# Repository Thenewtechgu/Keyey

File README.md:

# Keyey
A custom made 75 percent keyboard powered by the RP2040.

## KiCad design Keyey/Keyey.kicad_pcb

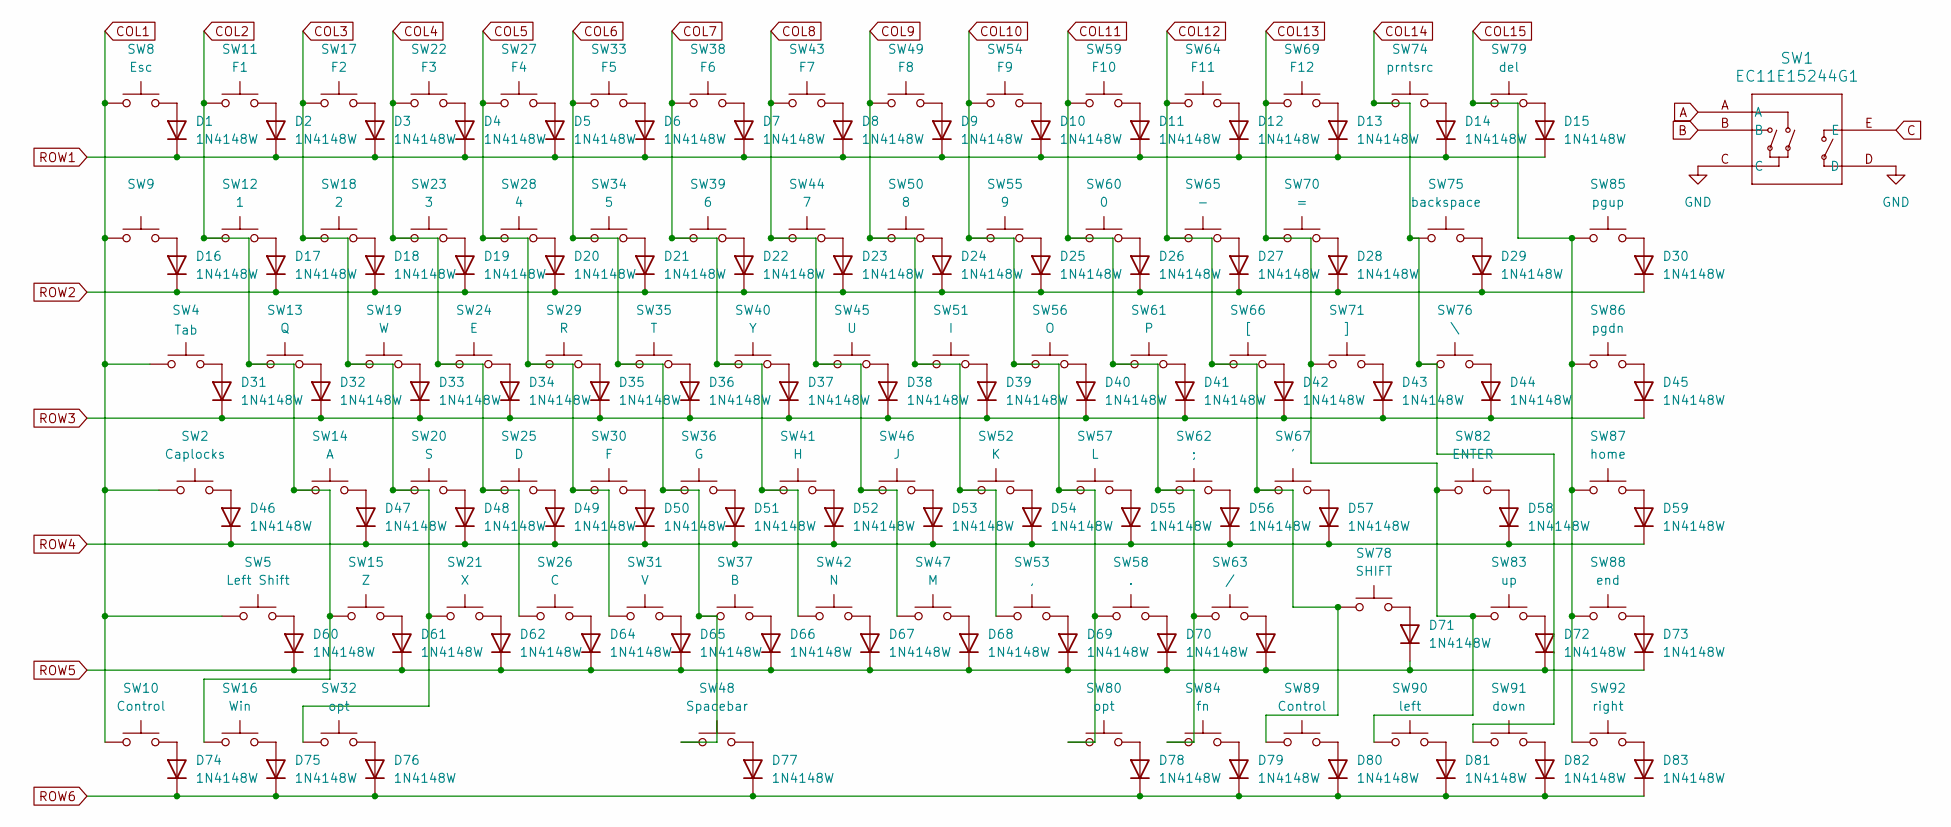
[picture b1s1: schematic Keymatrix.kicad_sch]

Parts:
D1, D2, D3, D4, D5, D6, D7, D8, D9, D10, D11, D12, D13, D14, D15, D16, D17, D18, D19, D20, D21, D22, D23, D24, D25, D26, D27, D28, D29, D30, D31, D32, D33, D34, D35, D36, D37, D38, D39, D40, D41, D42, D43, D44, D45, D46, D47, D48, D49, D50, D51, D52, D53, D54, D55, D56, D57, D58, D59, D60, D61, D62, D63, D64, D65, D66, D67, D68, D69, D70, D71, D72, D73, D74, D75, D76, D77, D78, D79, D80, D81, D82, D83: 1N4148W; D_SOD-123
SW1: EC11E15244G1; EC11E15244G1_AAL
SW2: Caplocks; SW_MX_1u
SW4: Tab; SW_MX_1u
SW5: Left Shift; SW_MX_1u
SW8: Esc; SW_MX_1u
SW9: SW_MX_1u
SW10, SW89: Control; SW_MX_1u
SW11: F1; SW_MX_1u
SW12: 1; SW_MX_1u
SW13: Q; SW_MX_1u
SW14: A; SW_MX_1u
SW15: Z; SW_MX_1u
SW16: Win; SW_MX_1u
SW17: F2; SW_MX_1u
SW18: 2; SW_MX_1u
SW19: W; SW_MX_1u
SW20: S; SW_MX_1u
SW21: X; SW_MX_1u
SW22: F3; SW_MX_1u
SW23: 3; SW_MX_1u
SW24: E; SW_MX_1u
SW25: D; SW_MX_1u
SW26: C; SW_MX_1u
SW27: F4; SW_MX_1u
SW28: 4; SW_MX_1u
SW29: R; SW_MX_1u
SW30: F; SW_MX_1u
SW31: V; SW_MX_1u
SW32, SW80: opt; SW_MX_1u
SW33: F5; SW_MX_1u
SW34: 5; SW_MX_1u
SW35: T; SW_MX_1u
SW36: G; SW_MX_1u
SW37: B; SW_MX_1u
SW38: F6; SW_MX_1u
SW39: 6; SW_MX_1u
SW40: Y; SW_MX_1u
SW41: H; SW_MX_1u
SW42: N; SW_MX_1u
SW43: F7; SW_MX_1u
SW44: 7; SW_MX_1u
SW45: U; SW_MX_1u
SW46: J; SW_MX_1u
SW47: M; SW_MX_1u
SW48: Spacebar; SW_MX_1u
SW49: F8; SW_MX_1u
SW50: 8; SW_MX_1u
SW51: I; SW_MX_1u
SW52: K; SW_MX_1u
SW53: ,; SW_MX_1u
SW54: F9; SW_MX_1u
SW55: 9; SW_MX_1u
SW56: O; SW_MX_1u
SW57: L; SW_MX_1u
SW58: .; SW_MX_1u
SW59: F10; SW_MX_1u
SW60: 0; SW_MX_1u
SW61: P; SW_MX_1u
SW62: ;; SW_MX_1u
SW63: /; SW_MX_1u
SW64: F11; SW_MX_1u
SW65: -; SW_MX_1u
SW66: [; SW_MX_1u
SW67: '; SW_MX_1u
SW69: F12; SW_MX_1u
SW70: =; SW_MX_1u
SW71: ]; SW_MX_1u
SW74: prntsrc; SW_MX_1u
SW75: backspace; SW_MX_1u
SW76: \; SW_MX_1u
SW78: SHIFT; SW_MX_1u
SW79: del; SW_MX_1u
SW82: ENTER; SW_MX_1u
SW83: up; SW_MX_1u
SW84: fn; SW_MX_1u
SW85: pgup; SW_MX_1u
SW86: pgdn; SW_MX_1u
SW87: home; SW_MX_1u
SW88: end; SW_MX_1u
SW90: left; SW_MX_1u
SW91: down; SW_MX_1u
SW92: right; SW_MX_1u

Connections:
A: SW1.A; also elsewhere on the board
B: SW1.B; also elsewhere on the board
COL1: SW2.1, SW4.1, SW5.1, SW8.1, SW9.1, SW10.1; also elsewhere on the board
COL2: SW11.1, SW12.1, SW13.1, SW14.1, SW15.1, SW16.1; also elsewhere on the board
COL3: SW17.1, SW18.1, SW19.1, SW20.1, SW21.1, SW32.1; also elsewhere on the board
COL4: SW22.1, SW23.1, SW24.1, SW25.1, SW26.1; also elsewhere on the board
COL5: SW27.1, SW28.1, SW29.1, SW30.1, SW31.1; also elsewhere on the board
COL6: SW33.1, SW34.1, SW35.1, SW36.1, SW37.1, SW48.1; also elsewhere on the board
COL7: SW38.1, SW39.1, SW40.1, SW41.1, SW42.1; also elsewhere on the board
COL8: SW43.1, SW44.1, SW45.1, SW46.1, SW47.1; also elsewhere on the board
COL9: SW49.1, SW50.1, SW51.1, SW52.1, SW53.1; also elsewhere on the board
COL10: SW54.1, SW55.1, SW56.1, SW57.1, SW58.1, SW80.1; also elsewhere on the board
COL11: SW59.1, SW60.1, SW61.1, SW62.1, SW63.1, SW84.1; also elsewhere on the board
COL12: SW64.1, SW65.1, SW66.1, SW67.1, SW78.1, SW89.1; also elsewhere on the board
COL13: SW69.1, SW70.1, SW71.1, SW82.1, SW83.1, SW90.1; also elsewhere on the board
COL14: SW74.1, SW75.1, SW76.1, SW91.1; also elsewhere on the board
COL15: SW79.1, SW85.1, SW86.1, SW87.1, SW88.1, SW92.1; also elsewhere on the board
GND: SW1.C, SW1.D; also elsewhere on the board
unnamed: D1.2 (A), SW8.2
unnamed: D2.2 (A), SW11.2
unnamed: D3.2 (A), SW17.2
unnamed: D4.2 (A), SW22.2
unnamed: D5.2 (A), SW27.2
unnamed: D6.2 (A), SW33.2
unnamed: D7.2 (A), SW38.2
unnamed: D8.2 (A), SW43.2
unnamed: D9.2 (A), SW49.2
unnamed: D10.2 (A), SW54.2
unnamed: D11.2 (A), SW59.2
unnamed: D12.2 (A), SW64.2
unnamed: D13.2 (A), SW69.2
unnamed: D14.2 (A), SW74.2
unnamed: D15.2 (A), SW79.2
unnamed: D16.2 (A), SW9.2
unnamed: D17.2 (A), SW12.2
unnamed: D18.2 (A), SW18.2
unnamed: D19.2 (A), SW23.2
unnamed: D20.2 (A), SW28.2
unnamed: D21.2 (A), SW34.2
unnamed: D22.2 (A), SW39.2
unnamed: D23.2 (A), SW44.2
unnamed: D24.2 (A), SW50.2
unnamed: D25.2 (A), SW55.2
unnamed: D26.2 (A), SW60.2
unnamed: D27.2 (A), SW65.2
unnamed: D28.2 (A), SW70.2
unnamed: D29.2 (A), SW75.2
unnamed: D30.2 (A), SW85.2
unnamed: D31.2 (A), SW4.2
unnamed: D32.2 (A), SW13.2
unnamed: D33.2 (A), SW19.2
unnamed: D34.2 (A), SW24.2
unnamed: D35.2 (A), SW29.2
unnamed: D36.2 (A), SW35.2
unnamed: D37.2 (A), SW40.2
unnamed: D38.2 (A), SW45.2
unnamed: D39.2 (A), SW51.2
unnamed: D40.2 (A), SW56.2
unnamed: D41.2 (A), SW61.2
unnamed: D42.2 (A), SW66.2
unnamed: D43.2 (A), SW71.2
unnamed: D44.2 (A), SW76.2
unnamed: D45.2 (A), SW86.2
unnamed: D46.2 (A), SW2.2
unnamed: D47.2 (A), SW14.2
unnamed: D48.2 (A), SW20.2
unnamed: D49.2 (A), SW25.2
unnamed: D50.2 (A), SW30.2
unnamed: D51.2 (A), SW36.2
unnamed: D52.2 (A), SW41.2
unnamed: D53.2 (A), SW46.2
unnamed: D54.2 (A), SW52.2
unnamed: D55.2 (A), SW57.2
unnamed: D56.2 (A), SW62.2
unnamed: D57.2 (A), SW67.2
unnamed: D58.2 (A), SW82.2
unnamed: D59.2 (A), SW87.2
unnamed: D60.2 (A), SW5.2
unnamed: D61.2 (A), SW15.2
unnamed: D62.2 (A), SW21.2
unnamed: D63.2 (A), SW63.2
unnamed: D64.2 (A), SW26.2
unnamed: D65.2 (A), SW31.2
unnamed: D66.2 (A), SW37.2
unnamed: D67.2 (A), SW42.2
unnamed: D68.2 (A), SW47.2
unnamed: D69.2 (A), SW53.2
unnamed: D70.2 (A), SW58.2
unnamed: D71.2 (A), SW78.2
unnamed: D72.2 (A), SW83.2
unnamed: D73.2 (A), SW88.2
unnamed: D74.2 (A), SW10.2
unnamed: D75.2 (A), SW16.2
unnamed: D76.2 (A), SW32.2
unnamed: D77.2 (A), SW48.2
unnamed: D78.2 (A), SW80.2
unnamed: D79.2 (A), SW84.2
unnamed: D80.2 (A), SW89.2
unnamed: D81.2 (A), SW90.2
unnamed: D82.2 (A), SW91.2
unnamed: D83.2 (A), SW92.2
ROW1: D1.1 (K), D2.1 (K), D3.1 (K), D4.1 (K), D5.1 (K), D6.1 (K), D7.1 (K), D8.1 (K), D9.1 (K), D10.1 (K), D11.1 (K), D12.1 (K), D13.1 (K), D14.1 (K), D15.1 (K); also elsewhere on the board
ROW2: D16.1 (K), D17.1 (K), D18.1 (K), D19.1 (K), D20.1 (K), D21.1 (K), D22.1 (K), D23.1 (K), D24.1 (K), D25.1 (K), D26.1 (K), D27.1 (K), D28.1 (K), D29.1 (K), D30.1 (K); also elsewhere on the board
ROW3: D31.1 (K), D32.1 (K), D33.1 (K), D34.1 (K), D35.1 (K), D36.1 (K), D37.1 (K), D38.1 (K), D39.1 (K), D40.1 (K), D41.1 (K), D42.1 (K), D43.1 (K), D44.1 (K), D45.1 (K); also elsewhere on the board
ROW4: D46.1 (K), D47.1 (K), D48.1 (K), D49.1 (K), D50.1 (K), D51.1 (K), D52.1 (K), D53.1 (K), D54.1 (K), D55.1 (K), D56.1 (K), D57.1 (K), D58.1 (K), D59.1 (K); also elsewhere on the board
ROW5: D60.1 (K), D61.1 (K), D62.1 (K), D63.1 (K), D64.1 (K), D65.1 (K), D66.1 (K), D67.1 (K), D68.1 (K), D69.1 (K), D70.1 (K), D71.1 (K), D72.1 (K), D73.1 (K); also elsewhere on the board
ROW6: D74.1 (K), D75.1 (K), D76.1 (K), D77.1 (K), D78.1 (K), D79.1 (K), D80.1 (K), D81.1 (K), D82.1 (K), D83.1 (K); also elsewhere on the board

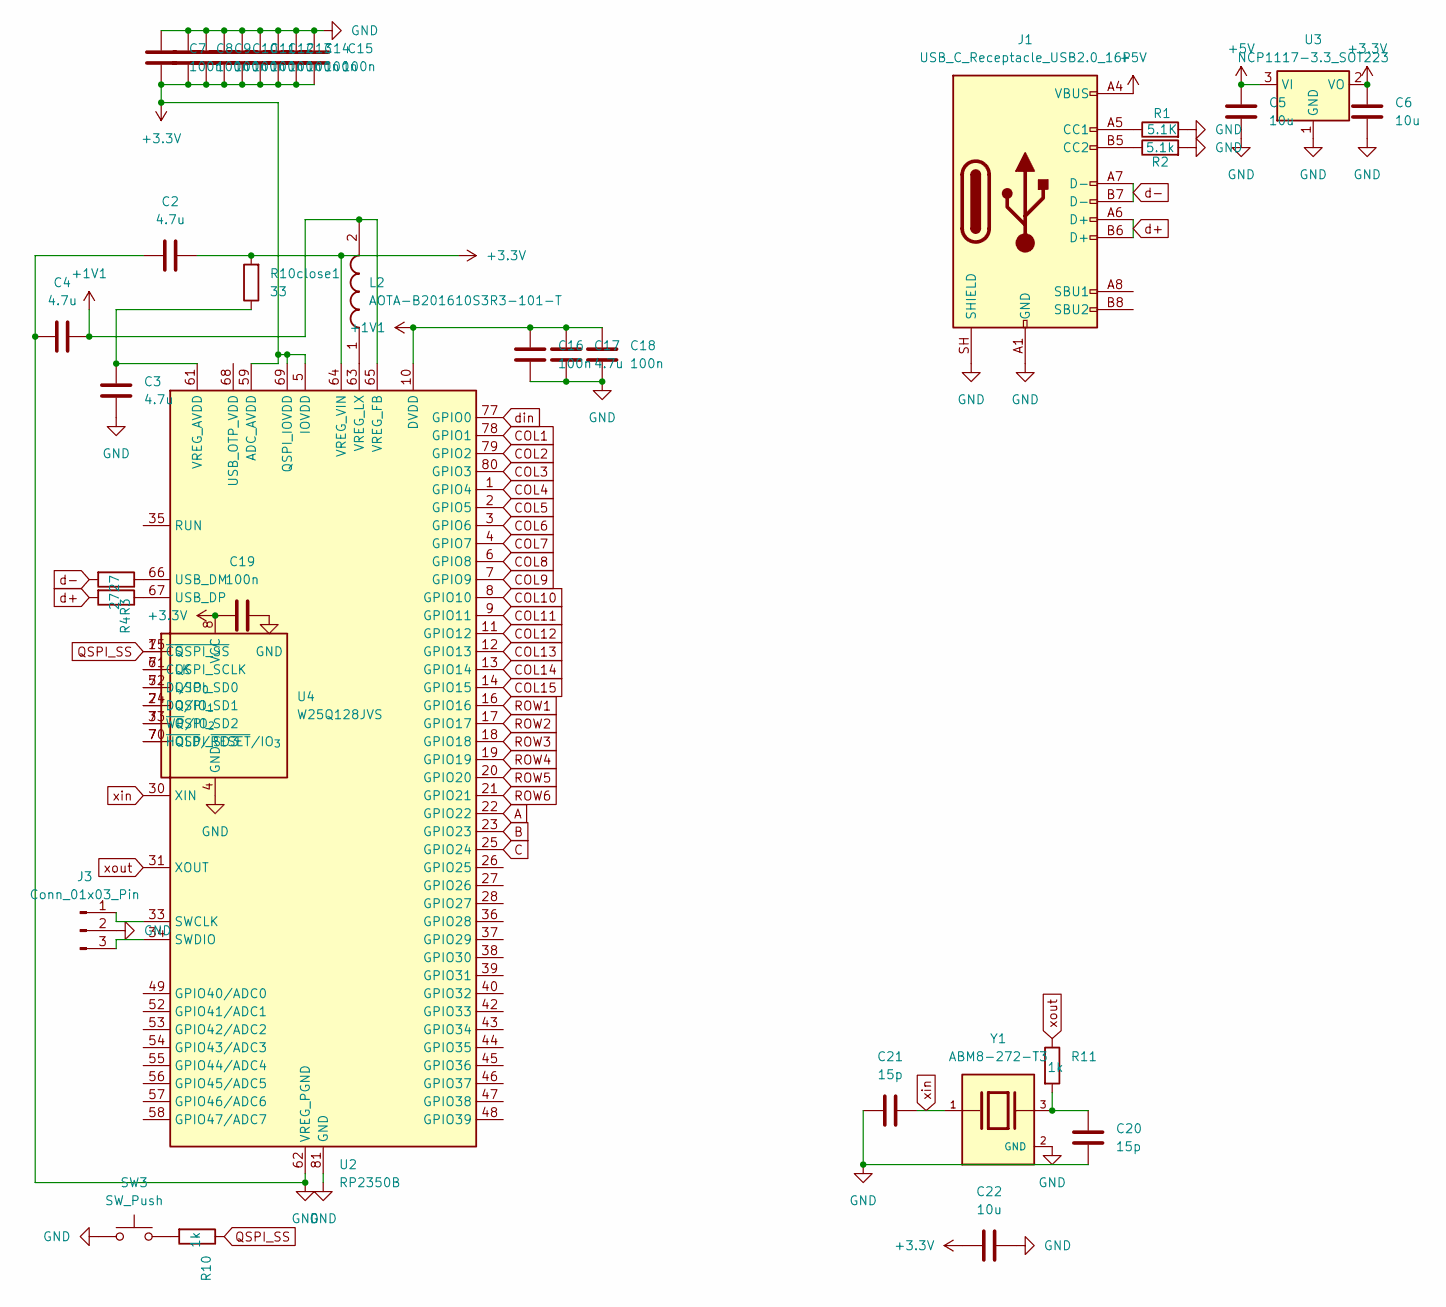
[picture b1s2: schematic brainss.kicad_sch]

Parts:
C2, C3, C4, C17: 4.7u; C_0402_1005Metric_Pad0.74x0.62mm_HandSolder
C5, C6: 10u; C_01005_0402Metric_Pad0.57x0.30mm_HandSolder
C7, C8, C9, C10, C11, C12, C13, C14, C15, C16, C18, C19: 100n; C_0402_1005Metric_Pad0.74x0.62mm_HandSolder
C20, C21: 15p; C_0402_1005Metric_Pad0.74x0.62mm_HandSolder
C22: 10u; C_0402_1005Metric_Pad0.74x0.62mm_HandSolder
J1: USB_C_Receptacle_USB2.0_16P; USB_C_Receptacle_Amphenol_12401948E412A
J3: Conn_01x03_Pin; PinHeader_1x03_P1.00mm_Vertical
L2: AOTA-B201610S3R3-101-T; AOTAB201610S3R3101T; Manufacturer_Part_Number AOTA-B201610S3R3-101-T; Mouser Part Number 815-AB201610S3R3101T
R1: 5.1K; R_01005_0402Metric_Pad0.57x0.30mm_HandSolder
R2: 5.1k; R_01005_0402Metric_Pad0.57x0.30mm_HandSolder
R3, R4: 27; R_0402_1005Metric_Pad0.72x0.64mm_HandSolder
R10, R11: 1k; R_0402_1005Metric_Pad0.72x0.64mm_HandSolder
R10close1: 33; R_0402_1005Metric_Pad0.72x0.64mm_HandSolder
SW3: SW_Push; Panasonic_EVQPUJ_EVQPUA
U2: RP2350B; QFN-80-1EP_10x10mm_P0.4mm_EP3.4x3.4mm
U3: NCP1117-3.3_SOT223; SOT-223-3_TabPin2
U4: W25Q128JVS; SOIC-8_5.3x5.3mm_P1.27mm
Y1: ABM8-272-T3; XTAL_ABM8-272-T3; PARTREV 07-29-20

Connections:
+1V1: C4.2, C16.2, C17.2, C18.2, L2.2, U2.10 (DVDD), U2.32 (DVDD), U2.51 (DVDD), U2.65 (VREG_FB)
+3.3V: C2.2, C6.2, C7.1, C8.1, C9.1, C10.1, C11.1, C12.1, C13.1, C14.1, C15.1, C19.2, C22.2, R10close1.2, U2.5 (IOVDD), U2.15 (IOVDD), U2.24 (IOVDD), U2.29 (IOVDD), U2.41 (IOVDD), U2.50 (IOVDD), U2.59 (ADC_AVDD), U2.60 (IOVDD), U2.64 (VREG_VIN), U2.69 (QSPI_IOVDD), U2.76 (IOVDD), U3.2 (VO), U4.8 (VCC)
+5V: C5.2, J1.A4 (VBUS), J1.A9 (VBUS), J1.B4 (VBUS), J1.B9 (VBUS), U3.3 (VI); also elsewhere on the board
A: U2.22 (GPIO22); also elsewhere on the board
B: U2.23 (GPIO23); also elsewhere on the board
C: U2.25 (GPIO24)
COL1: U2.78 (GPIO1); also elsewhere on the board
COL2: U2.79 (GPIO2); also elsewhere on the board
COL3: U2.80 (GPIO3); also elsewhere on the board
COL4: U2.1 (GPIO4); also elsewhere on the board
COL5: U2.2 (GPIO5); also elsewhere on the board
COL6: U2.3 (GPIO6); also elsewhere on the board
COL7: U2.4 (GPIO7); also elsewhere on the board
COL8: U2.6 (GPIO8); also elsewhere on the board
COL9: U2.7 (GPIO9); also elsewhere on the board
COL10: U2.8 (GPIO10); also elsewhere on the board
COL11: U2.9 (GPIO11); also elsewhere on the board
COL12: U2.11 (GPIO12); also elsewhere on the board
COL13: U2.12 (GPIO13); also elsewhere on the board
COL14: U2.13 (GPIO14); also elsewhere on the board
COL15: U2.14 (GPIO15); also elsewhere on the board
GND: C2.1, C3.1, C4.1, C5.1, C6.1, C7.2, C8.2, C9.2, C10.2, C11.2, C12.2, C13.2, C14.2, C15.2, C16.1, C17.1, C18.1, C19.1, C20.1, C21.2, C22.1, J1.A1 (GND), J1.A12 (GND), J1.B1 (GND), J1.B12 (GND), J1.SH (SHIELD), J3.2, R1.2, R2.2, SW3.1, U2.62 (VREG_PGND), U2.81 (GND), U3.1 (GND), U4.4 (GND), Y1.2 (GND), Y1.4 (GND); also elsewhere on the board
unnamed: C20.2, R11.2, Y1.3
unnamed: J1.A5 (CC1), R1.1
unnamed: J1.B5 (CC2), R2.1
unnamed: J3.1, U2.33 (SWCLK)
unnamed: J3.3, U2.34 (SWDIO)
unnamed: R10.2, SW3.2
unnamed: U2.71 (QSPI_SCLK), U4.6 (CLK)
unnamed: U2.72 (QSPI_SD0), U4.5 (DI/IO_{0})
unnamed: U2.74 (QSPI_SD1), U4.2 (DO/IO_{1})
unnamed: U2.73 (QSPI_SD2), U4.3 (~WP/IO_{2})
unnamed: U2.70 (QSPI_SD3), U4.7 (~HOLD/~RESET/IO_{3})
unnamed: R3.1, U2.66 (USB_DM)
unnamed: R4.1, U2.67 (USB_DP)
unnamed: C3.2, R10close1.1, U2.61 (VREG_AVDD)
unnamed: L2.1, U2.63 (VREG_LX)
QSPI_SS: R10.1, U2.75 (~QSPI_SS), U4.1 (~CS)
ROW1: U2.16 (GPIO16); also elsewhere on the board
ROW2: U2.17 (GPIO17); also elsewhere on the board
ROW3: U2.18 (GPIO18); also elsewhere on the board
ROW4: U2.19 (GPIO19); also elsewhere on the board
ROW5: U2.20 (GPIO20); also elsewhere on the board
ROW6: U2.21 (GPIO21); also elsewhere on the board
d+: J1.A6 (D+), J1.B6 (D+), R4.2
d-: J1.A7 (D-), J1.B7 (D-), R3.2
din: U2.77 (GPIO0); also elsewhere on the board
xin: C21.1, U2.30 (XIN), Y1.1
xout: R11.1, U2.31 (XOUT)

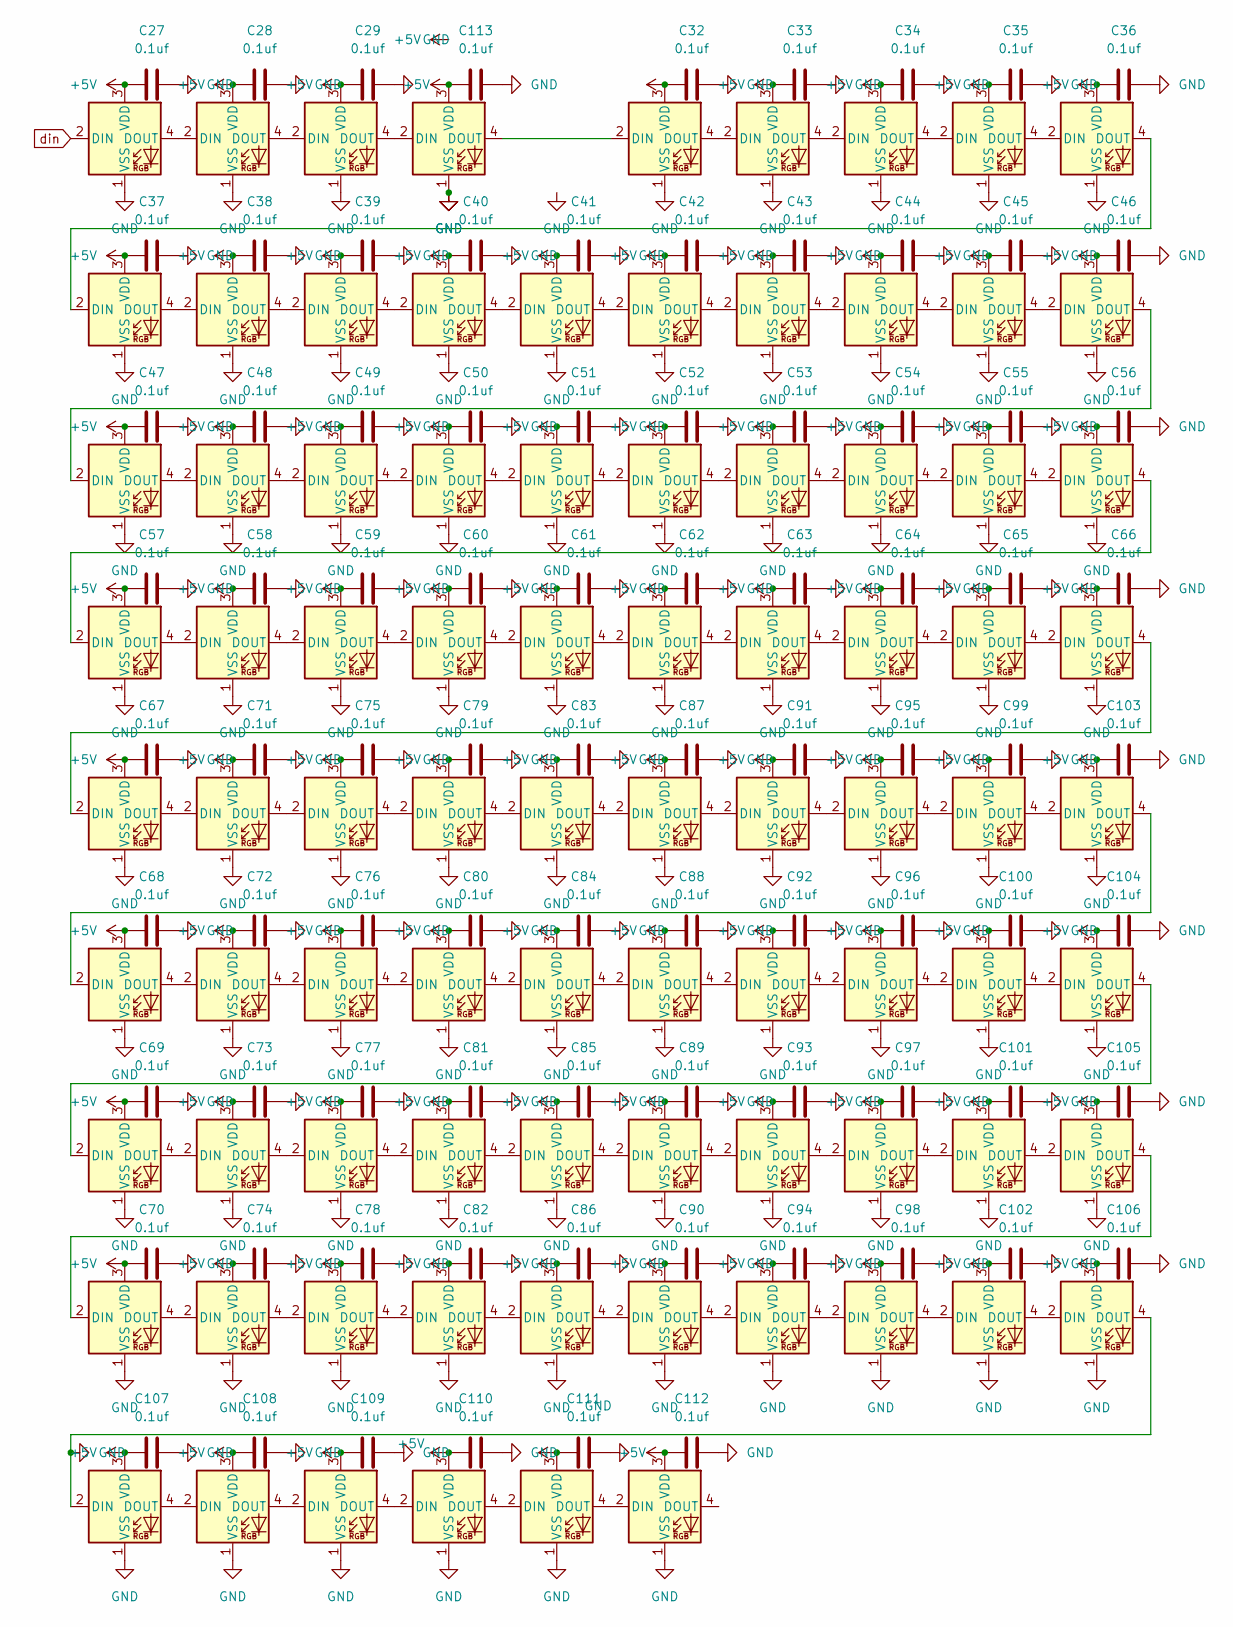
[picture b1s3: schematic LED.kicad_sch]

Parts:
C27, C28, C29, C32, C33, C34, C35, C36, C37, C38, C39, C40, C41, C42, C43, C44, C45, C46, C47, C48, C49, C50, C51, C52, C53, C54, C55, C56, C57, C58, C59, C60, C61, C62, C63, C64, C65, C66, C67, C68, C69, C70, C71, C72, C73, C74, C75, C76, C77, C78, C79, C80, C81, C82, C83, C84, C85, C86, C87, C88, C89, C90, C91, C92, C93, C94, C95, C96, C97, C98, C99, C100, C101, C102, C103, C104, C105, C106, C107, C108, C109, C110, C111, C112, C113: 0.1uf; C_01005_0402Metric_Pad0.57x0.30mm_HandSolder
D84, D85, D86, D87, D88, D93, D94, D95, D96, D97, D98, D99, D100, D101, D102, D103, D104, D105, D106, D107, D108, D109, D110, D111, D112, D113, D114, D115, D116, D117, D118, D119, D120, D121, D122, D123, D124, D125, D126, D127, D128, D129, D130, D131, D132, D133, D134, D135, D136, D137, D138, D139, D140, D141, D142, D143, D144, D145, D146, D147, D148, D149, D150, D151, D152, D153, D154, D155, D156, D157, D158, D159, D160, D161, D162, D163, D164, D165, D166, D167, D168, D169, D170, D171, D172: SK6812MINI-E; LED_SK6812MINI-E_3.2x2.8mm_P1.5mm_ReverseMount

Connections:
+5V: C27.1, C28.1, C29.1, C32.1, C33.1, C34.1, C35.1, C36.1, C37.1, C38.1, C39.1, C40.1, C41.1, C42.1, C43.1, C44.1, C45.1, C46.1, C47.1, C48.1, C49.1, C50.1, C51.1, C52.1, C53.1, C54.1, C55.1, C56.1, C57.1, C58.1, C59.1, C60.1, C61.1, C62.1, C63.1, C64.1, C65.1, C66.1, C67.1, C68.1, C69.1, C70.1, C71.1, C72.1, C73.1, C74.1, C75.1, C76.1, C77.1, C78.1, C79.1, C80.1, C81.1, C82.1, C83.1, C84.1, C85.1, C86.1, C87.1, C88.1, C89.1, C90.1, C91.1, C92.1, C93.1, C94.1, C95.1, C96.1, C97.1, C98.1, C99.1, C100.1, C101.1, C102.1, C103.1, C104.1, C105.1, C106.1, C107.1, C108.1, C109.1, C110.1, C111.1, C112.1, C113.1, D84.3 (VDD), D85.3 (VDD), D86.3 (VDD), D87.3 (VDD), D88.3 (VDD), D93.3 (VDD), D94.3 (VDD), D95.3 (VDD), D96.3 (VDD), D97.3 (VDD), D98.3 (VDD), D99.3 (VDD), D100.3 (VDD), D101.3 (VDD), D102.3 (VDD), D103.3 (VDD), D104.3 (VDD), D105.3 (VDD), D106.3 (VDD), D107.3 (VDD), D108.3 (VDD), D109.3 (VDD), D110.3 (VDD), D111.3 (VDD), D112.3 (VDD), D113.3 (VDD), D114.3 (VDD), D115.3 (VDD), D116.3 (VDD), D117.3 (VDD), D118.3 (VDD), D119.3 (VDD), D120.3 (VDD), D121.3 (VDD), D122.3 (VDD), D123.3 (VDD), D124.3 (VDD), D125.3 (VDD), D126.3 (VDD), D127.3 (VDD), D128.3 (VDD), D129.3 (VDD), D130.3 (VDD), D131.3 (VDD), D132.3 (VDD), D133.3 (VDD), D134.3 (VDD), D135.3 (VDD), D136.3 (VDD), D137.3 (VDD), D138.3 (VDD), D139.3 (VDD), D140.3 (VDD), D141.3 (VDD), D142.3 (VDD), D143.3 (VDD), D144.3 (VDD), D145.3 (VDD), D146.3 (VDD), D147.3 (VDD), D148.3 (VDD), D149.3 (VDD), D150.3 (VDD), D151.3 (VDD), D152.3 (VDD), D153.3 (VDD), D154.3 (VDD), D155.3 (VDD), D156.3 (VDD), D157.3 (VDD), D158.3 (VDD), D159.3 (VDD), D160.3 (VDD), D161.3 (VDD), D162.3 (VDD), D163.3 (VDD), D164.3 (VDD), D165.3 (VDD), D166.3 (VDD), D167.3 (VDD), D168.3 (VDD), D169.3 (VDD), D170.3 (VDD), D171.3 (VDD), D172.3 (VDD); also elsewhere on the board
GND: C27.2, C28.2, C29.2, C32.2, C33.2, C34.2, C35.2, C36.2, C37.2, C38.2, C39.2, C40.2, C41.2, C42.2, C43.2, C44.2, C45.2, C46.2, C47.2, C48.2, C49.2, C50.2, C51.2, C52.2, C53.2, C54.2, C55.2, C56.2, C57.2, C58.2, C59.2, C60.2, C61.2, C62.2, C63.2, C64.2, C65.2, C66.2, C67.2, C68.2, C69.2, C70.2, C71.2, C72.2, C73.2, C74.2, C75.2, C76.2, C77.2, C78.2, C79.2, C80.2, C81.2, C82.2, C83.2, C84.2, C85.2, C86.2, C87.2, C88.2, C89.2, C90.2, C91.2, C92.2, C93.2, C94.2, C95.2, C96.2, C97.2, C98.2, C99.2, C100.2, C101.2, C102.2, C103.2, C104.2, C105.2, C106.2, C107.2, C108.2, C109.2, C110.2, C111.2, C112.2, C113.2, D84.1 (VSS), D85.1 (VSS), D86.1 (VSS), D87.1 (VSS), D88.1 (VSS), D93.1 (VSS), D94.1 (VSS), D95.1 (VSS), D96.1 (VSS), D97.1 (VSS), D98.1 (VSS), D99.1 (VSS), D100.1 (VSS), D101.1 (VSS), D102.1 (VSS), D103.1 (VSS), D104.1 (VSS), D105.1 (VSS), D106.1 (VSS), D107.1 (VSS), D108.1 (VSS), D109.1 (VSS), D110.1 (VSS), D111.1 (VSS), D112.1 (VSS), D113.1 (VSS), D114.1 (VSS), D115.1 (VSS), D116.1 (VSS), D117.1 (VSS), D118.1 (VSS), D119.1 (VSS), D120.1 (VSS), D121.1 (VSS), D122.1 (VSS), D123.1 (VSS), D124.1 (VSS), D125.1 (VSS), D126.1 (VSS), D127.1 (VSS), D128.1 (VSS), D129.1 (VSS), D130.1 (VSS), D131.1 (VSS), D132.1 (VSS), D133.1 (VSS), D134.1 (VSS), D135.1 (VSS), D136.1 (VSS), D137.1 (VSS), D138.1 (VSS), D139.1 (VSS), D140.1 (VSS), D141.1 (VSS), D142.1 (VSS), D143.1 (VSS), D144.1 (VSS), D145.1 (VSS), D146.1 (VSS), D147.1 (VSS), D148.1 (VSS), D149.1 (VSS), D150.1 (VSS), D151.1 (VSS), D152.1 (VSS), D153.1 (VSS), D154.1 (VSS), D155.1 (VSS), D156.1 (VSS), D157.1 (VSS), D158.1 (VSS), D159.1 (VSS), D160.1 (VSS), D161.1 (VSS), D162.1 (VSS), D163.1 (VSS), D164.1 (VSS), D165.1 (VSS), D165.4 (DOUT), D166.1 (VSS), D166.2 (DIN), D167.1 (VSS), D168.1 (VSS), D169.1 (VSS), D170.1 (VSS), D171.1 (VSS), D172.1 (VSS); also elsewhere on the board
unnamed: D84.4 (DOUT), D85.2 (DIN)
unnamed: D85.4 (DOUT), D86.2 (DIN)
unnamed: D87.4 (DOUT), D88.2 (DIN)
unnamed: D88.4 (DOUT), D93.2 (DIN)
unnamed: D93.4 (DOUT), D94.2 (DIN)
unnamed: D94.4 (DOUT), D95.2 (DIN)
unnamed: D95.4 (DOUT), D96.2 (DIN)
unnamed: D96.4 (DOUT), D97.2 (DIN)
unnamed: D97.4 (DOUT), D98.2 (DIN)
unnamed: D98.4 (DOUT), D99.2 (DIN)
unnamed: D99.4 (DOUT), D100.2 (DIN)
unnamed: D100.4 (DOUT), D101.2 (DIN)
unnamed: D101.4 (DOUT), D102.2 (DIN)
unnamed: D102.4 (DOUT), D103.2 (DIN)
unnamed: D103.4 (DOUT), D104.2 (DIN)
unnamed: D104.4 (DOUT), D105.2 (DIN)
unnamed: D105.4 (DOUT), D106.2 (DIN)
unnamed: D106.4 (DOUT), D107.2 (DIN)
unnamed: D107.4 (DOUT), D108.2 (DIN)
unnamed: D108.4 (DOUT), D109.2 (DIN)
unnamed: D109.4 (DOUT), D110.2 (DIN)
unnamed: D110.4 (DOUT), D111.2 (DIN)
unnamed: D111.4 (DOUT), D112.2 (DIN)
unnamed: D112.4 (DOUT), D113.2 (DIN)
unnamed: D113.4 (DOUT), D114.2 (DIN)
unnamed: D114.4 (DOUT), D115.2 (DIN)
unnamed: D115.4 (DOUT), D116.2 (DIN)
unnamed: D116.4 (DOUT), D117.2 (DIN)
unnamed: D117.4 (DOUT), D118.2 (DIN)
unnamed: D118.4 (DOUT), D119.2 (DIN)
unnamed: D119.4 (DOUT), D120.2 (DIN)
unnamed: D120.4 (DOUT), D121.2 (DIN)
unnamed: D121.4 (DOUT), D122.2 (DIN)
unnamed: D122.4 (DOUT), D123.2 (DIN)
unnamed: D123.4 (DOUT), D124.2 (DIN)
unnamed: D124.4 (DOUT), D125.2 (DIN)
unnamed: D125.4 (DOUT), D126.2 (DIN)
unnamed: D126.4 (DOUT), D130.2 (DIN)
unnamed: D127.2 (DIN), D162.4 (DOUT)
unnamed: D127.4 (DOUT), D131.2 (DIN)
unnamed: D128.2 (DIN), D163.4 (DOUT)
unnamed: D128.4 (DOUT), D132.2 (DIN)
unnamed: D129.2 (DIN), D164.4 (DOUT)
unnamed: D129.4 (DOUT), D133.2 (DIN)
unnamed: D130.4 (DOUT), D134.2 (DIN)
unnamed: D131.4 (DOUT), D135.2 (DIN)
unnamed: D132.4 (DOUT), D136.2 (DIN)
unnamed: D133.4 (DOUT), D137.2 (DIN)
unnamed: D134.4 (DOUT), D138.2 (DIN)
unnamed: D135.4 (DOUT), D139.2 (DIN)
unnamed: D136.4 (DOUT), D140.2 (DIN)
unnamed: D137.4 (DOUT), D141.2 (DIN)
unnamed: D138.4 (DOUT), D142.2 (DIN)
unnamed: D139.4 (DOUT), D143.2 (DIN)
unnamed: D140.4 (DOUT), D144.2 (DIN)
unnamed: D141.4 (DOUT), D145.2 (DIN)
unnamed: D142.4 (DOUT), D146.2 (DIN)
unnamed: D143.4 (DOUT), D147.2 (DIN)
unnamed: D144.4 (DOUT), D148.2 (DIN)
unnamed: D145.4 (DOUT), D149.2 (DIN)
unnamed: D146.4 (DOUT), D150.2 (DIN)
unnamed: D147.4 (DOUT), D151.2 (DIN)
unnamed: D148.4 (DOUT), D152.2 (DIN)
unnamed: D149.4 (DOUT), D153.2 (DIN)
unnamed: D150.4 (DOUT), D154.2 (DIN)
unnamed: D151.4 (DOUT), D155.2 (DIN)
unnamed: D152.4 (DOUT), D156.2 (DIN)
unnamed: D153.4 (DOUT), D157.2 (DIN)
unnamed: D154.4 (DOUT), D158.2 (DIN)
unnamed: D155.4 (DOUT), D159.2 (DIN)
unnamed: D156.4 (DOUT), D160.2 (DIN)
unnamed: D157.4 (DOUT), D161.2 (DIN)
unnamed: D158.4 (DOUT), D162.2 (DIN)
unnamed: D159.4 (DOUT), D163.2 (DIN)
unnamed: D160.4 (DOUT), D164.2 (DIN)
unnamed: D161.4 (DOUT), D165.2 (DIN)
unnamed: D166.4 (DOUT), D167.2 (DIN)
unnamed: D167.4 (DOUT), D168.2 (DIN)
unnamed: D168.4 (DOUT), D169.2 (DIN)
unnamed: D169.4 (DOUT), D170.2 (DIN)
unnamed: D170.4 (DOUT), D171.2 (DIN)
unnamed: D86.4 (DOUT), D172.2 (DIN)
unnamed: D87.2 (DIN), D172.4 (DOUT)
din: D84.2 (DIN); also elsewhere on the board

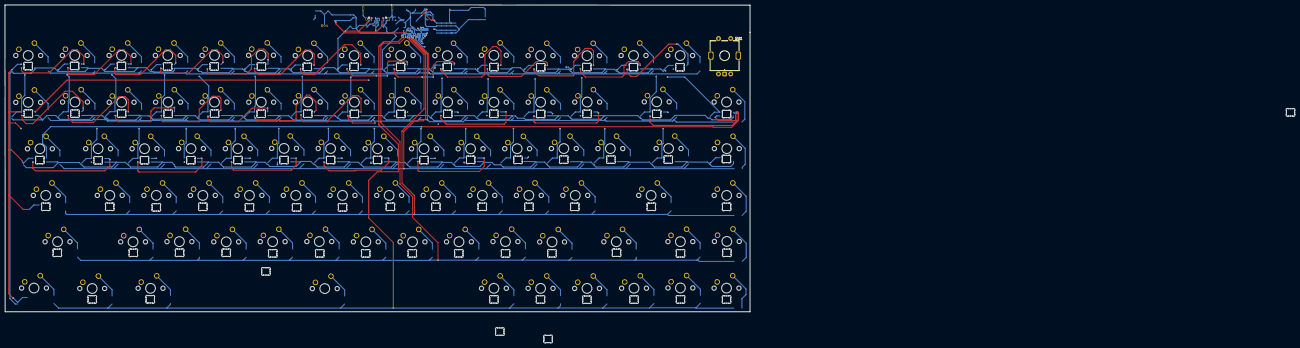
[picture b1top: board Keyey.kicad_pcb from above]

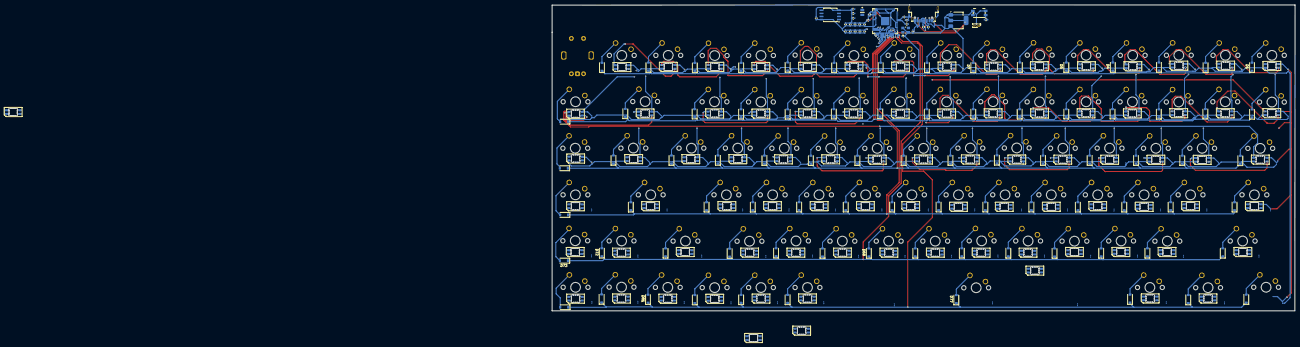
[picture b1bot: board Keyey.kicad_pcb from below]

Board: 4 copper layers, 304.8 x 125.5 mm, 373 parts (289 on the bottom side), 214 nets.

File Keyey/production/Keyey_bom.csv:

Designator,Footprint,Quantity,Value,LCSC Part #
"C10, C11, C12, C13, C14, C15, C16, C18, C19, C7, C8, C9",0402,12,100n,
"C100, C101, C102, C103, C104, C105, C106, C107, C108, C109, C110, C111, C112, C113, C27, C28, C29, C32, C33, C34, C35, C36, C37, C38, C39, C40, C41, C42, C43, C44, C45, C46, C47, C48, C49, C50, C51, C52, C53, C54, C55, C56, C57, C58, C59, C60, C61, C62, C63, C64, C65, C66, C67, C68, C69, C70, C71, C72, C73, C74, C75, C76, C77, C78, C79, C80, C81, C82, C83, C84, C85, C86, C87, C88, C89, C90, C91, C92, C93, C94, C95, C96, C97, C98, C99",01005,85,0.1uf,
"C17, C2, C3, C4",0402,4,4.7u,
"C20, C21",0402,2,15p,
C22,0402,1,10u,
"C5, C6",01005,2,10u,
"D1, D10, D11, D12, D13, D14, D15, D16, D17, D18, D19, D2, D20, D21, D22, D23, D24, D25, D26, D27, D28, D29, D3, D30, D31, D32, D33, D34, D35, D36, D37, D38, D39, D4, D40, D41, D42, D43, D44, D45, D46, D47, D48, D49, D5, D50, D51, D52, D53, D54, D55, D56, D57, D58, D59, D6, D60, D61, D62, D63, D64, D65, D66, D67, D68, D69, D7, D70, D71, D72, D73, D74, D75, D76, D77, D78, D79, D8, D80, D81, D82, D83, D9",D_SOD-123,83,1N4148W,
"D100, D101, D102, D103, D104, D105, D106, D107, D108, D109, D110, D111, D112, D113, D114, D115, D116, D117, D118, D119, D120, D121, D122, D123, D124, D125, D126, D127, D128, D129, D130, D131, D132, D133, D134, D135, D136, D137, D138, D139, D140, D141, D142, D143, D144, D145, D146, D147, D148, D149, D150, D151, D152, D153, D154, D155, D156, D157, D158, D159, D160, D161, D162, D163, D164, D165, D166, D167, D168, D169, D170, D171, D172, D84, D85, D86, D87, D88, D93, D94, D95, D96, D97, D98, D99",LED_SK6812MINI-E_3.2x2.8mm_P1.5mm_ReverseMount,85,SK6812MINI-E,
J1,USB_C_Receptacle_Amphenol_12401948E412A,1,USB_C_Receptacle_USB2.0_16P,
L2,AOTAB201610S3R3101T,1,AOTA-B201610S3R3-101-T,
"R1, R2",01005,2,5.1K,
"R10, R11, R12",0402,3,1k,
R10CLOSE1,0402,1,33,
"R3, R4",0402,2,27,
"SW10, SW89",SW_MX_1u,2,Control,
SW11,SW_MX_1u,1,F1,
SW12,SW_MX_1u,1,1,
SW13,SW_MX_1u,1,Q,
SW14,SW_MX_1u,1,A,
SW15,SW_MX_1u,1,Z,
SW16,SW_MX_1u,1,Win,
SW17,SW_MX_1u,1,F2,
SW18,SW_MX_1u,1,2,
SW19,SW_MX_1u,1,W,
SW2,SW_MX_1u,1,Caplocks,
SW20,SW_MX_1u,1,S,
SW21,SW_MX_1u,1,X,
SW22,SW_MX_1u,1,F3,
SW23,SW_MX_1u,1,3,
SW24,SW_MX_1u,1,E,
SW25,SW_MX_1u,1,D,
SW26,SW_MX_1u,1,C,
SW27,SW_MX_1u,1,F4,
SW28,SW_MX_1u,1,4,
SW29,SW_MX_1u,1,R,
"SW3, SW7",Panasonic_EVQPUJ_EVQPUA,2,SW_Push,
SW30,SW_MX_1u,1,F,
SW31,SW_MX_1u,1,V,
"SW32, SW80",SW_MX_1u,2,opt,
SW33,SW_MX_1u,1,F5,
SW34,SW_MX_1u,1,5,
SW35,SW_MX_1u,1,T,
SW36,SW_MX_1u,1,G,
SW37,SW_MX_1u,1,B,
SW38,SW_MX_1u,1,F6,
SW39,SW_MX_1u,1,6,
SW4,SW_MX_1u,1,Tab,
SW40,SW_MX_1u,1,Y,
SW41,SW_MX_1u,1,H,
SW42,SW_MX_1u,1,N,
SW43,SW_MX_1u,1,F7,
SW44,SW_MX_1u,1,7,
SW45,SW_MX_1u,1,U,
SW46,SW_MX_1u,1,J,
SW47,SW_MX_1u,1,M,
SW48,SW_MX_1u,1,Spacebar,
SW49,SW_MX_1u,1,F8,
SW5,SW_MX_1u,1,Left Shift,
SW50,SW_MX_1u,1,8,
SW51,SW_MX_1u,1,I,
SW52,SW_MX_1u,1,K,
SW53,SW_MX_1u,1,",",
SW54,SW_MX_1u,1,F9,
SW55,SW_MX_1u,1,9,
SW56,SW_MX_1u,1,O,
SW57,SW_MX_1u,1,L,
SW58,SW_MX_1u,1,.,
SW59,SW_MX_1u,1,F10,
SW6,RotaryEncoder_Alps_EC11E-Switch_Vertical_H20mm,1,RotaryEncoder_Switch_MP,
SW60,SW_MX_1u,1,0,
SW61,SW_MX_1u,1,P,
SW62,SW_MX_1u,1,;,
SW63,SW_MX_1u,1,/,
SW64,SW_MX_1u,1,F11,
SW65,SW_MX_1u,1,-,
SW66,SW_MX_1u,1,[,
SW67,SW_MX_1u,1,',
SW69,SW_MX_1u,1,F12,
SW70,SW_MX_1u,1,=,
SW71,SW_MX_1u,1,],
SW74,SW_MX_1u,1,prntsrc,
SW75,SW_MX_1u,1,backspace,
SW76,SW_MX_1u,1,\,
SW78,SW_MX_1u,1,SHIFT,
SW79,SW_MX_1u,1,del,
SW8,SW_MX_1u,1,Esc,
SW82,SW_MX_1u,1,ENTER,
SW83,SW_MX_1u,1,up,
SW84,SW_MX_1u,1,fn,
SW85,SW_MX_1u,1,pgup,
SW86,SW_MX_1u,1,pgdn,
SW87,SW_MX_1u,1,home,
SW88,SW_MX_1u,1,end,
SW9,SW_MX_1u,1,~,
SW90,SW_MX_1u,1,left,
SW91,SW_MX_1u,1,down,
SW92,SW_MX_1u,1,right,
U2,QFN-80-1EP_10x10mm_P0.4mm_EP3.4x3.4mm,1,RP2350B,
U3,SOT-223-3_TabPin2,1,NCP1117-3.3_SOT223,
U4,SOIC-8_5.3x5.3mm_P1.27mm,1,W25Q128JVS,
Y1,XTAL_ABM8-272-T3,1,ABM8-272-T3,
